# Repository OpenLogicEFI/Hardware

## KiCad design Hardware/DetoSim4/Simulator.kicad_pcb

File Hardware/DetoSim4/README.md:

# DetonStim

www.detonationems.com

Engine Simulator for Speeduino fork or Ardustim - https://github.com/speeduino/Ardu-Stim

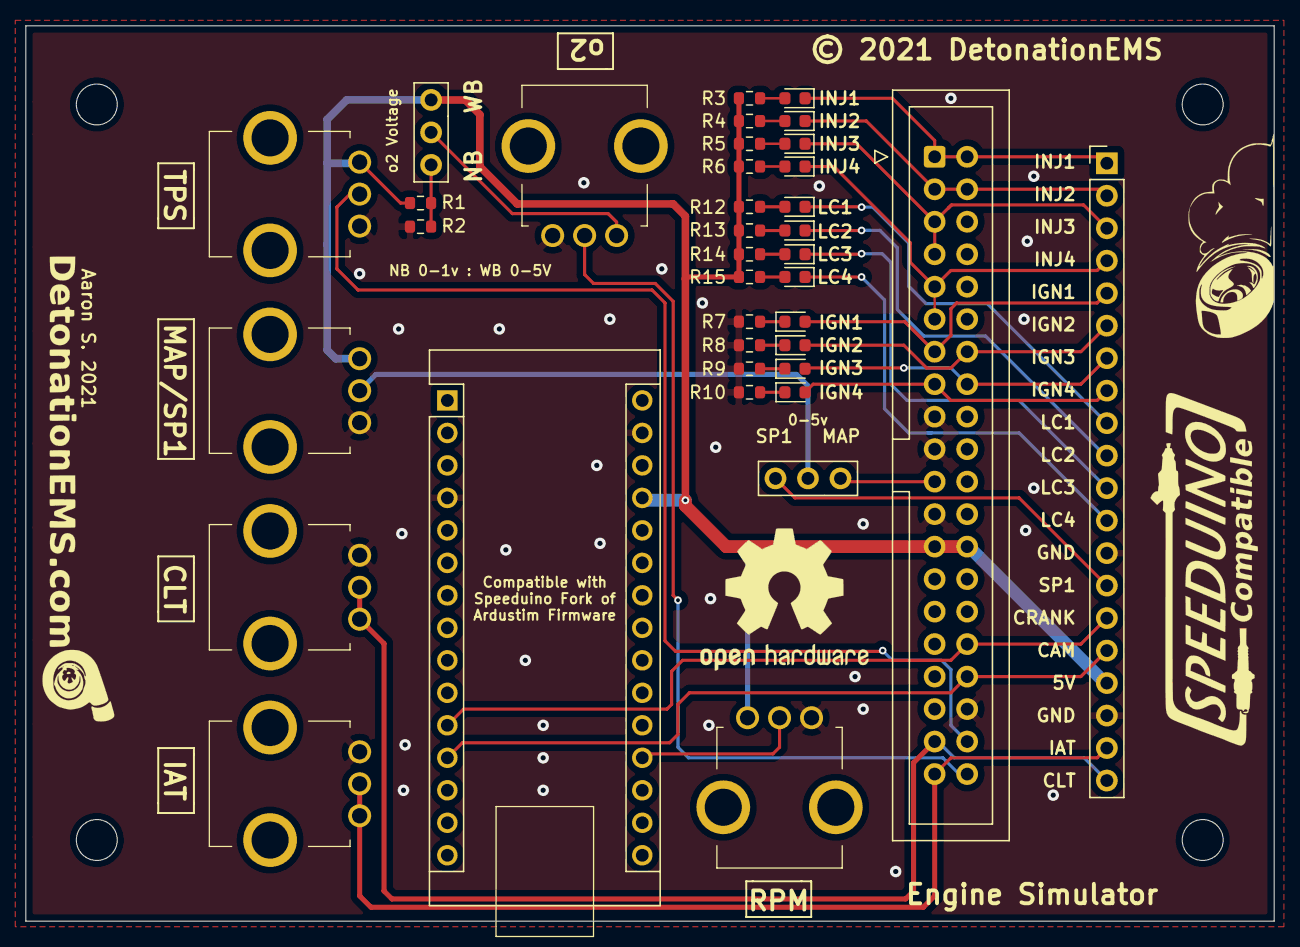
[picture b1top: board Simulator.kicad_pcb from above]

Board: 2 copper layers, 97.6 x 70.0 mm, 45 parts (0 on the bottom side), 38 nets.

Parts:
A1: Arduino_Nano_v3.x; Arduino_Nano
G1: Logo_Open_Hardware_Small; TireSmoke-22mm
G2: Logo_Open_Hardware_Small; DetonationEMS
G3: Logo_Open_Hardware_Small; SpeeduinoCompatible-30mm
G4: Logo_Open_Hardware_Small; OSHW-Logo2_14.6x12mm_SilkScreen
H1, H2, H3, H4: MountingHole; MountingHole_3.2mm_M3
J1, J8: Conn_01x03; 3-PinSwitch
J2: Conn_02x20_Counter_Clockwise; IDC-Header_2x20_P2.54mm_Vertical_Speeduino
J6: Header; PinHeader_1x20_P2.54mm_Vertical
LED1: INJ1; LED_0603_1608Metric
LED2: INJ2; LED_0603_1608Metric
LED3: INJ3; LED_0603_1608Metric
LED4: INJ4; LED_0603_1608Metric
LED5: IGN1; LED_0603_1608Metric
LED6: IGN2; LED_0603_1608Metric
LED7: IGN3; LED_0603_1608Metric
LED8: IGN4; LED_0603_1608Metric
LED10: IDLE; LED_0603_1608Metric
LED11: IDLE2; LED_0603_1608Metric
LED12: VVT; LED_0603_1608Metric
LED13: BOOST; LED_0603_1608Metric
POT1: IAT; RV09AF4020KB10K
POT2: CLT; RV09AF4020KB10K
POT3: TPS; RV09AF4020KB10K
POT4: MAP/SP1; RV09AF4020KB10K
POT5: o2; RV09AF4020KB10K
POT6: RPM; RV09AF4020KB10K
R1: 470; R_0603_1608Metric
R2: 100; R_0603_1608Metric
R3, R4, R5, R6, R7, R8, R9, R10, R12, R13, R14, R15: 330; R_0603_1608Metric

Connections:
+5V: A1.27, J1.1, J2.13, J2.28, J6.17, POT3.3, POT4.3, POT6.3, R1.1, R3.1, R4.1, R5.1, R6.1, R12.1, R13.1, R14.1, R15.1
CAM: A1.12, J2.24, J6.16
CLT: J2.19, J6.20, POT2.1, POT2.2
CRANK: A1.11, J2.25, J6.15
GND: A1.4, A1.29, J2.9, J2.10, J2.12, J2.23, J6.13, J6.18, POT1.3, POT2.3, POT3.1, POT4.1, POT5.1, POT6.1, R2.2, R7.1, R8.1, R9.1, R10.1
IAT: J2.20, J6.19, POT1.1, POT1.2
IGN1: J2.7, J6.5, LED5.2
IGN2: J2.34, J6.6, LED6.2
IGN3: J2.33, J6.7, LED7.2
IGN4: J2.8, J6.8, LED8.2
INJ1: J2.1, J2.40, J6.1, LED1.1
INJ2: J2.2, J2.39, J6.2, LED2.1
INJ3: J2.3, J2.4, J6.3, LED3.1
INJ4: J2.5, J2.6, J6.4, LED4.1
LC1: J6.9, LED10.1
LC2: J6.10, LED11.1
LC3: J6.11, LED12.1
LC4: J6.12, LED13.1
MAP: J2.11, J8.1
MC-A0: A1.19, POT6.2
unnamed: J1.3, R1.2, R2.1
unnamed: LED1.2, R3.2
unnamed: LED2.2, R4.2
unnamed: LED3.2, R5.2
unnamed: LED4.2, R6.2
unnamed: LED5.1, R7.2
unnamed: LED6.1, R8.2
unnamed: LED7.1, R9.2
unnamed: LED8.1, R10.2
unnamed: LED10.2, R12.2
unnamed: LED11.2, R13.2
unnamed: LED12.2, R14.2
unnamed: LED13.2, R15.2
RV4: J8.2, POT4.2
SP1: J6.14, J8.3
TPS: J2.22, POT3.2
o2: J2.21, POT5.2
o2-Voltage: J1.2, POT5.3

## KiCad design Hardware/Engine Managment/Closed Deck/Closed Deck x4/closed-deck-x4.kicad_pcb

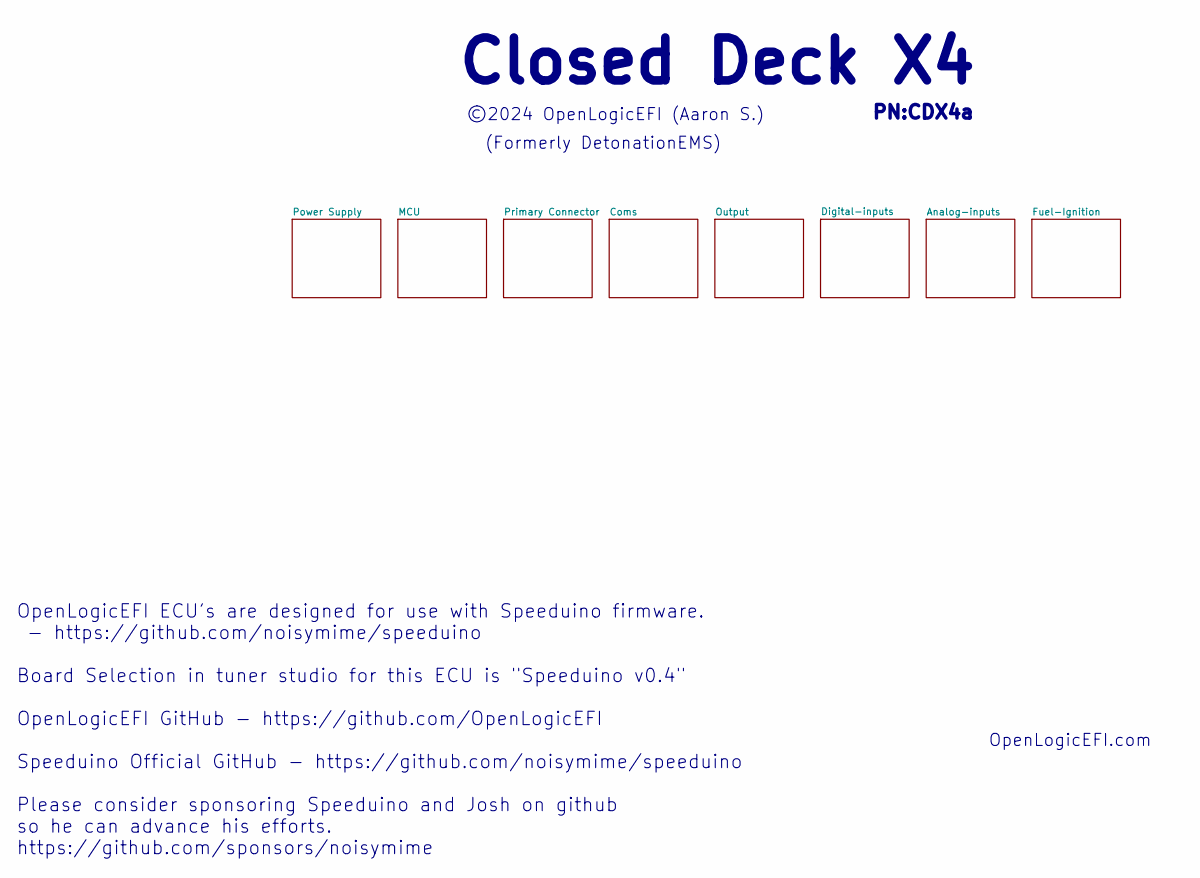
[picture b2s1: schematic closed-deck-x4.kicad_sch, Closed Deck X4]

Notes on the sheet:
©2024 OpenLogicEFI (Aaron S.)
(Formerly DetonationEMS)
OpenLogicEFI ECU's are designed for use with Speeduino firmware. - https://github.com/noisymime/speeduino Board Selection in tuner studio for this ECU is "Speeduino v0.4" OpenLogicEFI GitHub - https://github.com/OpenLogicEFI Speeduino Official GitHub - https://github.com/noisymime/speeduino Please 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
Closed Deck X4
PN:CDX4a
OpenLogicEFI.com

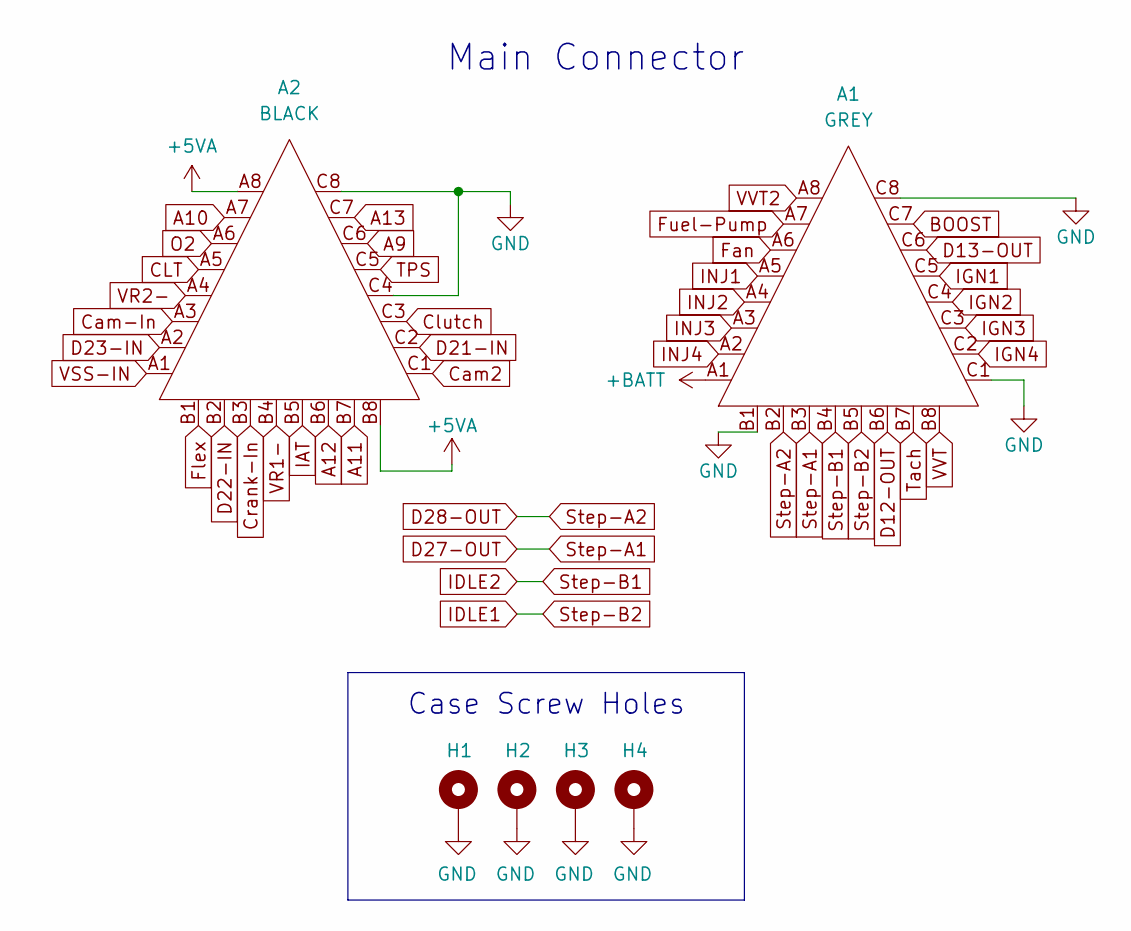
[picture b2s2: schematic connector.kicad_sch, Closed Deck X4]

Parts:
A1: GREY; Delphi_Sicma_24_Grey
A2: BLACK; Delphi_Sicma_24_Black
H1, H2, H3, H4: MountingHole_Pad; MountingHole_3.5mm_Pad

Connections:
+5V: A2.A8, A2.B8; also elsewhere on the board
+BATT: A1.A1; also elsewhere on the board
A9: A2.C6; also elsewhere on the board
A10: A2.A7; also elsewhere on the board
A11: A2.B7; also elsewhere on the board
A12: A2.B6; also elsewhere on the board
A13: A2.C7; also elsewhere on the board
BOOST: A1.C7; also elsewhere on the board
CLT: A2.A5; also elsewhere on the board
Cam2: A2.C1; also elsewhere on the board
Cam-In: A2.A3; also elsewhere on the board
Clutch: A2.C3; also elsewhere on the board
Crank-In: A2.B3; also elsewhere on the board
D12-OUT: A1.B6; also elsewhere on the board
D13-OUT: A1.C6; also elsewhere on the board
D21-IN: A2.C2; also elsewhere on the board
D22-IN: A2.B2; also elsewhere on the board
D23-IN: A2.A2; also elsewhere on the board
D27-OUT: A1.B3; also elsewhere on the board
D28-OUT: A1.B2; also elsewhere on the board
Fan: A1.A6; also elsewhere on the board
Flex: A2.B1; also elsewhere on the board
Fuel-Pump: A1.A7; also elsewhere on the board
GND: A1.B1, A1.C1, A1.C8, A2.C4, A2.C8, H1.1, H2.1, H3.1, H4.1; also elsewhere on the board
IAT: A2.B5; also elsewhere on the board
IDLE1: A1.B5; also elsewhere on the board
IDLE2: A1.B4; also elsewhere on the board
IGN1: A1.C5; also elsewhere on the board
IGN2: A1.C4; also elsewhere on the board
IGN3: A1.C3; also elsewhere on the board
IGN4: A1.C2; also elsewhere on the board
INJ1: A1.A5; also elsewhere on the board
INJ2: A1.A4; also elsewhere on the board
INJ3: A1.A3; also elsewhere on the board
INJ4: A1.A2; also elsewhere on the board
O2: A2.A6; also elsewhere on the board
TPS: A2.C5; also elsewhere on the board
Tach: A1.B7; also elsewhere on the board
VR1-: A2.B4; also elsewhere on the board
VR2-: A2.A4; also elsewhere on the board
VSS-IN: A2.A1; also elsewhere on the board
VVT: A1.B8; also elsewhere on the board
VVT2: A1.A8; also elsewhere on the board

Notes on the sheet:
Case Screw Holes
Main Connector

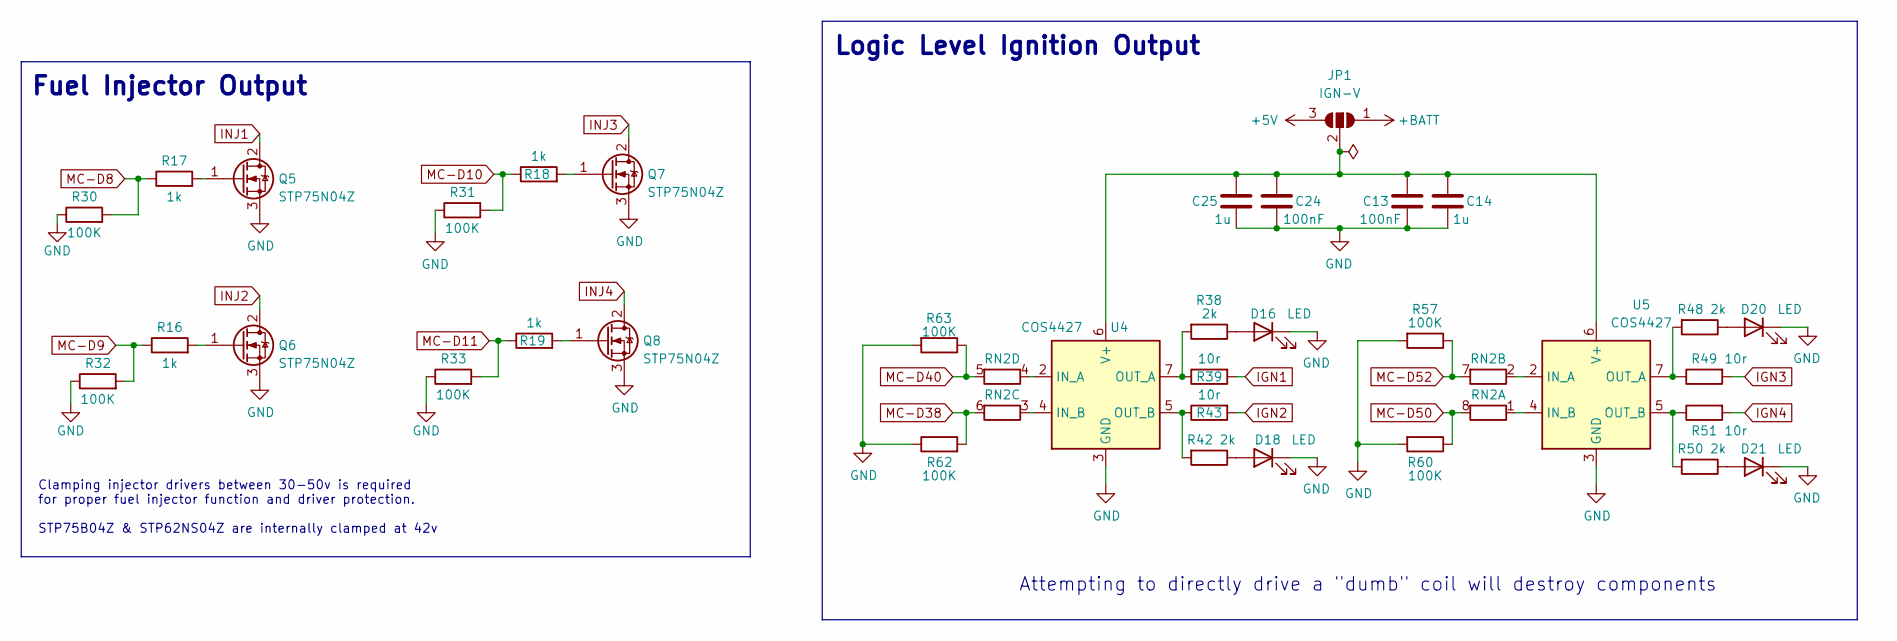
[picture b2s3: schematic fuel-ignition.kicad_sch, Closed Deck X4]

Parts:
C13, C24: 100nF; C_0402_1005Metric; LCSC C307331
C14, C25: 1u; C_0402_1005Metric; LCSC C52923
D16, D18, D20, D21: LED; LED_0603_1608Metric; Manufacture Part Number KT-0603R; LCSC C2286
JP1: IGN-V; 1x03-Proto
Q5, Q6, Q7, Q8: STP75N04Z; TO-220-3_Vertical
R16, R17, R18, R19: 1k; R_0402_1005Metric; Manufacture Part Number 0402WGF1001TCE; LCSC C11702
R30, R31, R32, R33, R57, R60, R62, R63: 100K; R_0402_1005Metric; Manufacture Part Number 0402WGF1003TCE; LCSC C25741
R38, R42, R48, R50: 2k; R_0402_1005Metric; Manufacture Part Number 0402WGF2001TCE; LCSC C4109
R39, R43, R49, R51: 10r; R_0805_2012Metric; Manufacture Part Number 0805W8F100JT5E; LCSC C17415
RN2: 1k; R_Array_Concave_4x0603; Manufacture Part Number 4D03WGJ0102T5E; LCSC C20197
U4, U5: COS4427; SOIC-8_3.9x4.9mm_P1.27mm; LCSC C2685358

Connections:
+5V: JP1.3 (B); also elsewhere on the board
+BATT: JP1.1 (A); also elsewhere on the board
GND: C13.2, C14.2, C24.2, C25.2, D16.1 (K), D18.1 (K), D20.1 (K), D21.1 (K), Q5.3 (S), Q6.3 (S), Q7.3 (S), Q8.3 (S), R30.1, R31.1, R32.1, R33.1, R57.2, R60.2, R62.1, R63.2, U4.3 (GND), U5.3 (GND); also elsewhere on the board
IGN1: R39.2; also elsewhere on the board
IGN2: R43.2; also elsewhere on the board
IGN3: R49.2; also elsewhere on the board
IGN4: R51.2; also elsewhere on the board
INJ1: Q5.2 (D); also elsewhere on the board
INJ2: Q6.2 (D); also elsewhere on the board
INJ3: Q7.2 (D); also elsewhere on the board
INJ4: Q8.2 (D); also elsewhere on the board
MC-D8: R17.1, R30.2; also elsewhere on the board
MC-D9: R16.1, R32.2; also elsewhere on the board
MC-D10: R18.1, R31.2; also elsewhere on the board
MC-D11: R19.1, R33.2; also elsewhere on the board
MC-D38: R62.2, RN2.6 (R3.2); also elsewhere on the board
MC-D40: R63.1, RN2.5 (R4.2); also elsewhere on the board
MC-D50: R60.1, RN2.8 (R1.2); also elsewhere on the board
MC-D52: R57.1, RN2.7 (R2.2); also elsewhere on the board
unnamed: D16.2 (A), R38.1
unnamed: D18.2 (A), R42.1
unnamed: D20.2 (A), R48.1
unnamed: D21.2 (A), R50.1
unnamed: C13.1, C14.1, C24.1, C25.1, JP1.2 (C), U4.6 (V+), U5.6 (V+)
unnamed: Q5.1 (G), R17.2
unnamed: Q6.1 (G), R16.2
unnamed: Q7.1 (G), R18.2
unnamed: Q8.1 (G), R19.2
unnamed: RN2.1 (R1.1), U5.4 (IN_B)
unnamed: RN2.2 (R2.1), U5.2 (IN_A)
unnamed: RN2.3 (R3.1), U4.4 (IN_B)
unnamed: RN2.4 (R4.1), U4.2 (IN_A)
unnamed: R38.2, R39.1, U4.7 (OUT_A)
unnamed: R42.2, R43.1, U4.5 (OUT_B)
unnamed: R48.2, R49.1, U5.7 (OUT_A)
unnamed: R50.2, R51.1, U5.5 (OUT_B)

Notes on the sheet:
Clamping injector drivers between 30-50v is required for proper fuel injector function and driver protection. STP75B04Z & STP62NS04Z are internally clamped at 42v
Fuel Injector Output
Logic Level Ignition Output
Attempting to directly drive a "dumb" coil will destroy components

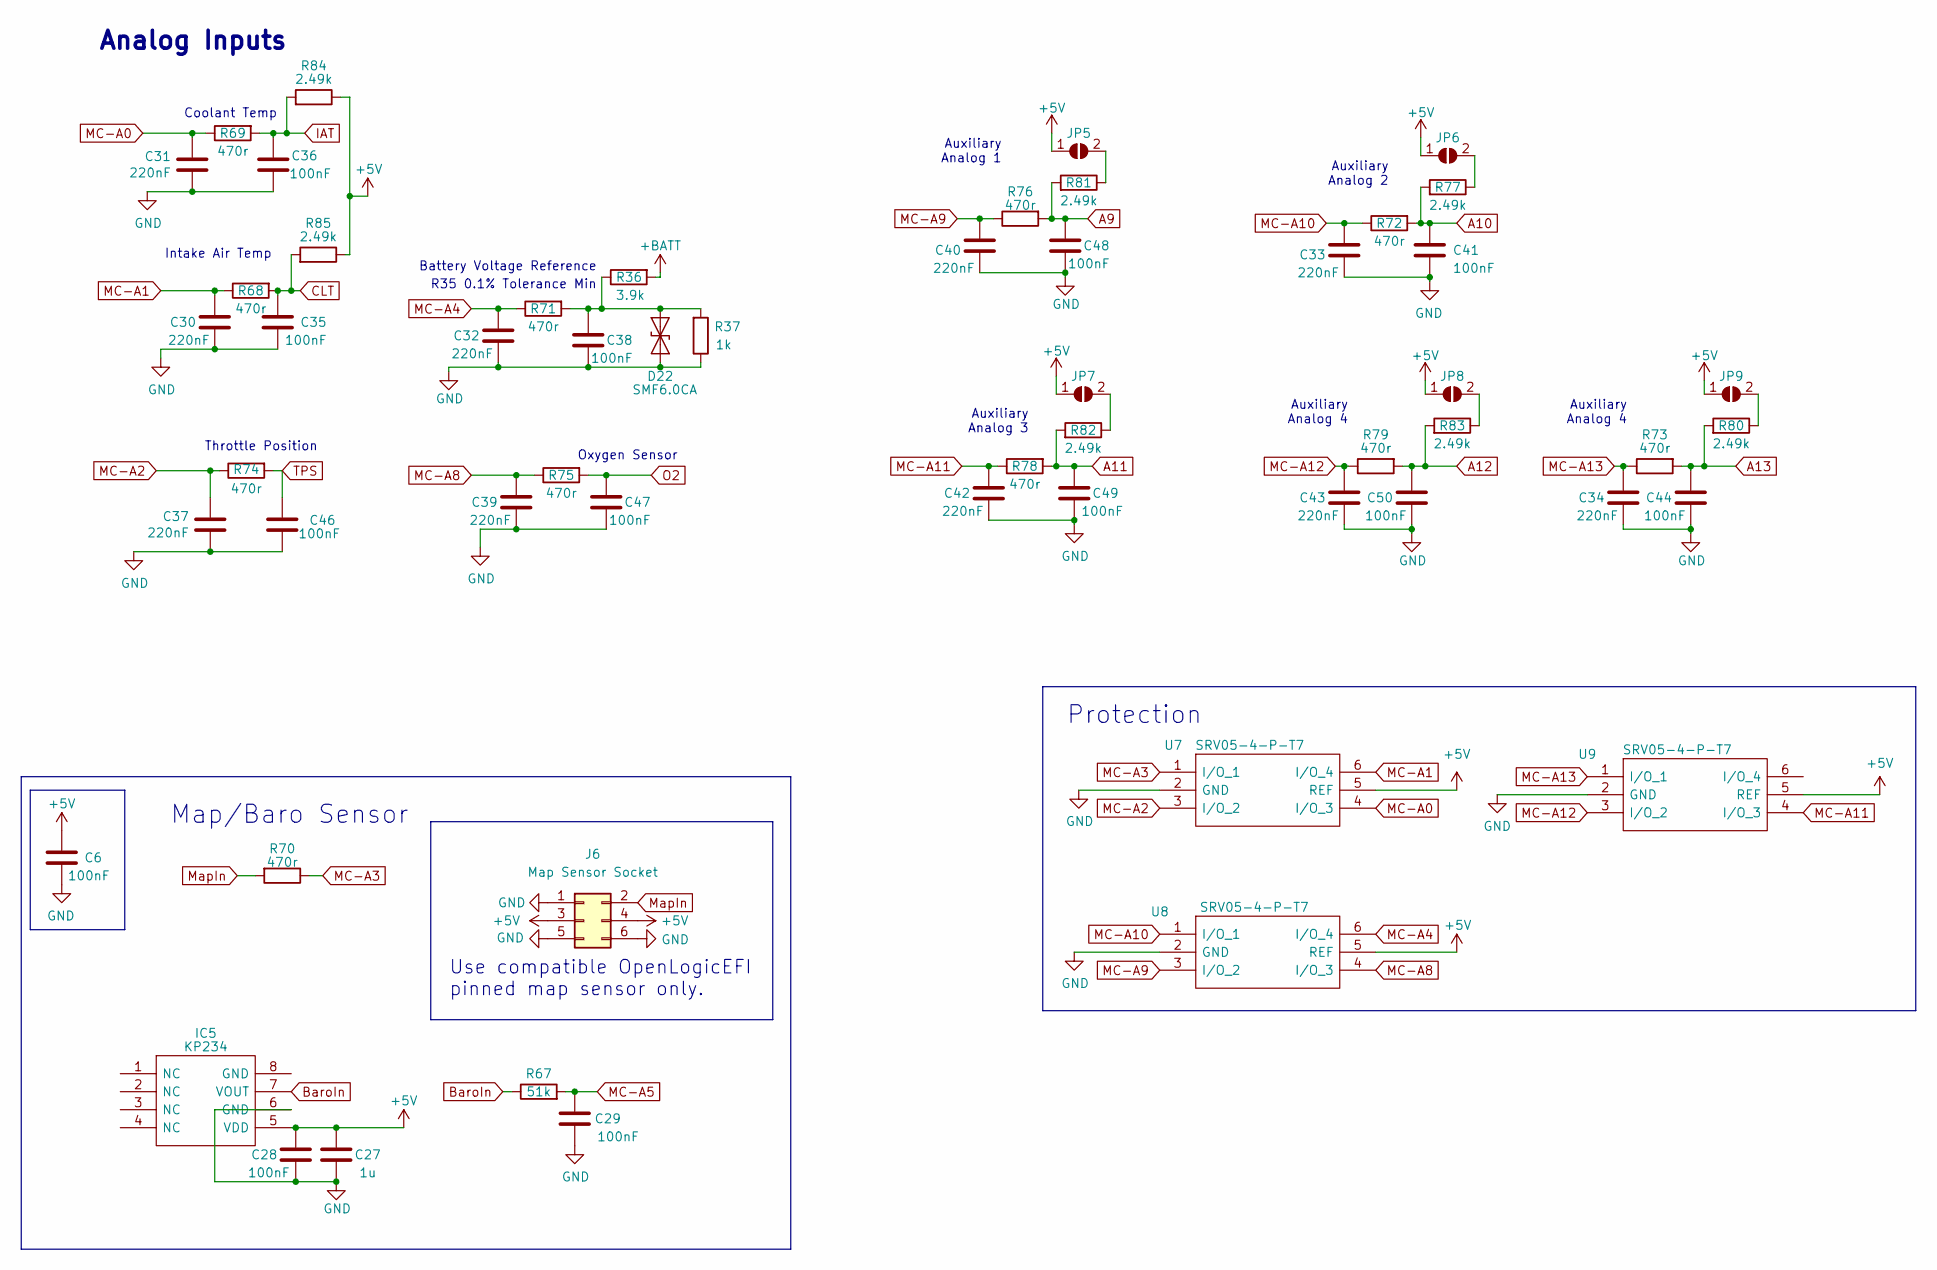
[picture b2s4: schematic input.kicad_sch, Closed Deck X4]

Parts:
C6, C28, C35, C36, C38, C41, C44, C46, C47, C48, C49, C50: 100nF; C_0402_1005Metric; LCSC C307331
C27: 1u; C_0402_1005Metric; LCSC C52923
C29: 100nF; C_0402_1005Metric; Manufacture Part Number CL05B104KB54PNC; LCSC C307331
C30, C31, C32, C33, C34, C37, C39, C40, C42, C43: 220nF; C_0402_1005Metric; LCSC C16772
D22: SMF6.0CA; D_SOD-123F; LCSC C2990473
IC5: KP234; KP234-Handsoldering; Mouser Part Number 726-KP234XTMA1
J6: Map Sensor Socket; PinSocket 2x03
JP5, JP6, JP7, JP8, JP9: SolderJumper_2_Open; SolderJumper-2_P1.3mm_Open_RoundedPad1.0x1.5mm
R36: 3.9k; R_0603_1608Metric; Manufacture Part Number 0603WAF3901T5E; LCSC C23018
R37: 1k; R_0402_1005Metric; Manufacture Part Number 0402WGF1001TCE; LCSC C11702
R67: 51k; R_0402_1005Metric; Manufacture Part Number 0402WGF5102TCE; LCSC C25794
R68, R69, R70, R71, R72, R73, R74, R75, R76, R78, R79: 470r; R_0402_1005Metric; Manufacture Part Number 0402WGF4700TCE; LCSC C25117
R77, R80, R81, R82, R83, R84, R85: 2.49k; R_0402_1005Metric; Manufacture Part Number RC0402FR-072K49L; LCSC C145071
U7, U8, U9: SRV05-4-P-T7; SOT-23-6; LCSC C85364

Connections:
+5V: C6.2, C27.1, C28.1, IC5.5 (VDD), J6.3, J6.4, JP5.1 (A), JP6.1 (A), JP7.1 (A), JP8.1 (A), JP9.1 (A), R84.1, R85.1, U7.5 (REF), U8.5 (REF), U9.5 (REF); also elsewhere on the board
+BATT: R36.2; also elsewhere on the board
A9: C48.1, R76.2, R81.2; also elsewhere on the board
A10: C41.1, R72.2, R77.2; also elsewhere on the board
A11: C49.1, R78.2, R82.2; also elsewhere on the board
A12: C50.1, R79.2, R83.2; also elsewhere on the board
A13: C44.1, R73.2, R80.2; also elsewhere on the board
BaroIn: IC5.7 (VOUT), R67.1
CLT: C35.1, R68.2, R85.2; also elsewhere on the board
GND: C6.1, C27.2, C28.2, C29.2, C30.2, C31.2, C32.2, C33.2, C34.2, C35.2, C36.2, C37.2, C38.2, C39.2, C40.2, C41.2, C42.2, C43.2, C44.2, C46.2, C47.2, C48.2, C49.2, C50.2, D22.2 (A2), IC5.6 (GND), J6.1, J6.5, J6.6, R37.1, U7.2 (GND), U8.2 (GND), U9.2 (GND); also elsewhere on the board
IAT: C36.1, R69.2, R84.2; also elsewhere on the board
MC-A0: C31.1, R69.1, U7.4 (I/O_3); also elsewhere on the board
MC-A1: C30.1, R68.1, U7.6 (I/O_4); also elsewhere on the board
MC-A2: C37.1, R74.1, U7.3 (I/O_2); also elsewhere on the board
MC-A3: R70.1, U7.1 (I/O_1); also elsewhere on the board
MC-A4: C32.1, R71.1, U8.6 (I/O_4); also elsewhere on the board
MC-A5: C29.1, R67.2; also elsewhere on the board
MC-A8: C39.1, R75.1, U8.4 (I/O_3); also elsewhere on the board
MC-A9: C40.1, R76.1, U8.3 (I/O_2); also elsewhere on the board
MC-A10: C33.1, R72.1, U8.1 (I/O_1); also elsewhere on the board
MC-A11: C42.1, R78.1, U9.4 (I/O_3); also elsewhere on the board
MC-A12: C43.1, R79.1, U9.3 (I/O_2); also elsewhere on the board
MC-A13: C34.1, R73.1, U9.1 (I/O_1); also elsewhere on the board
MapIn: J6.2, R70.2
unnamed: C38.1, D22.1 (A1), R36.1, R37.2, R71.2
unnamed: JP5.2 (B), R81.1
unnamed: JP6.2 (B), R77.1
unnamed: JP7.2 (B), R82.1
unnamed: JP8.2 (B), R83.1
unnamed: JP9.2 (B), R80.1
O2: C47.1, R75.2; also elsewhere on the board
TPS: C46.1, R74.2; also elsewhere on the board

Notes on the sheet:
Analog Inputs
Throttle Position
Auxiliary Analog 2
Auxiliary Analog 4
Auxiliary Analog 1
R35 0.1% Tolerance Min
Oxygen Sensor
Map/Baro Sensor
Use compatible OpenLogicEFI pinned map sensor only.
Coolant Temp
Intake Air Temp
Battery Voltage Reference
Protection
Auxiliary Analog 3

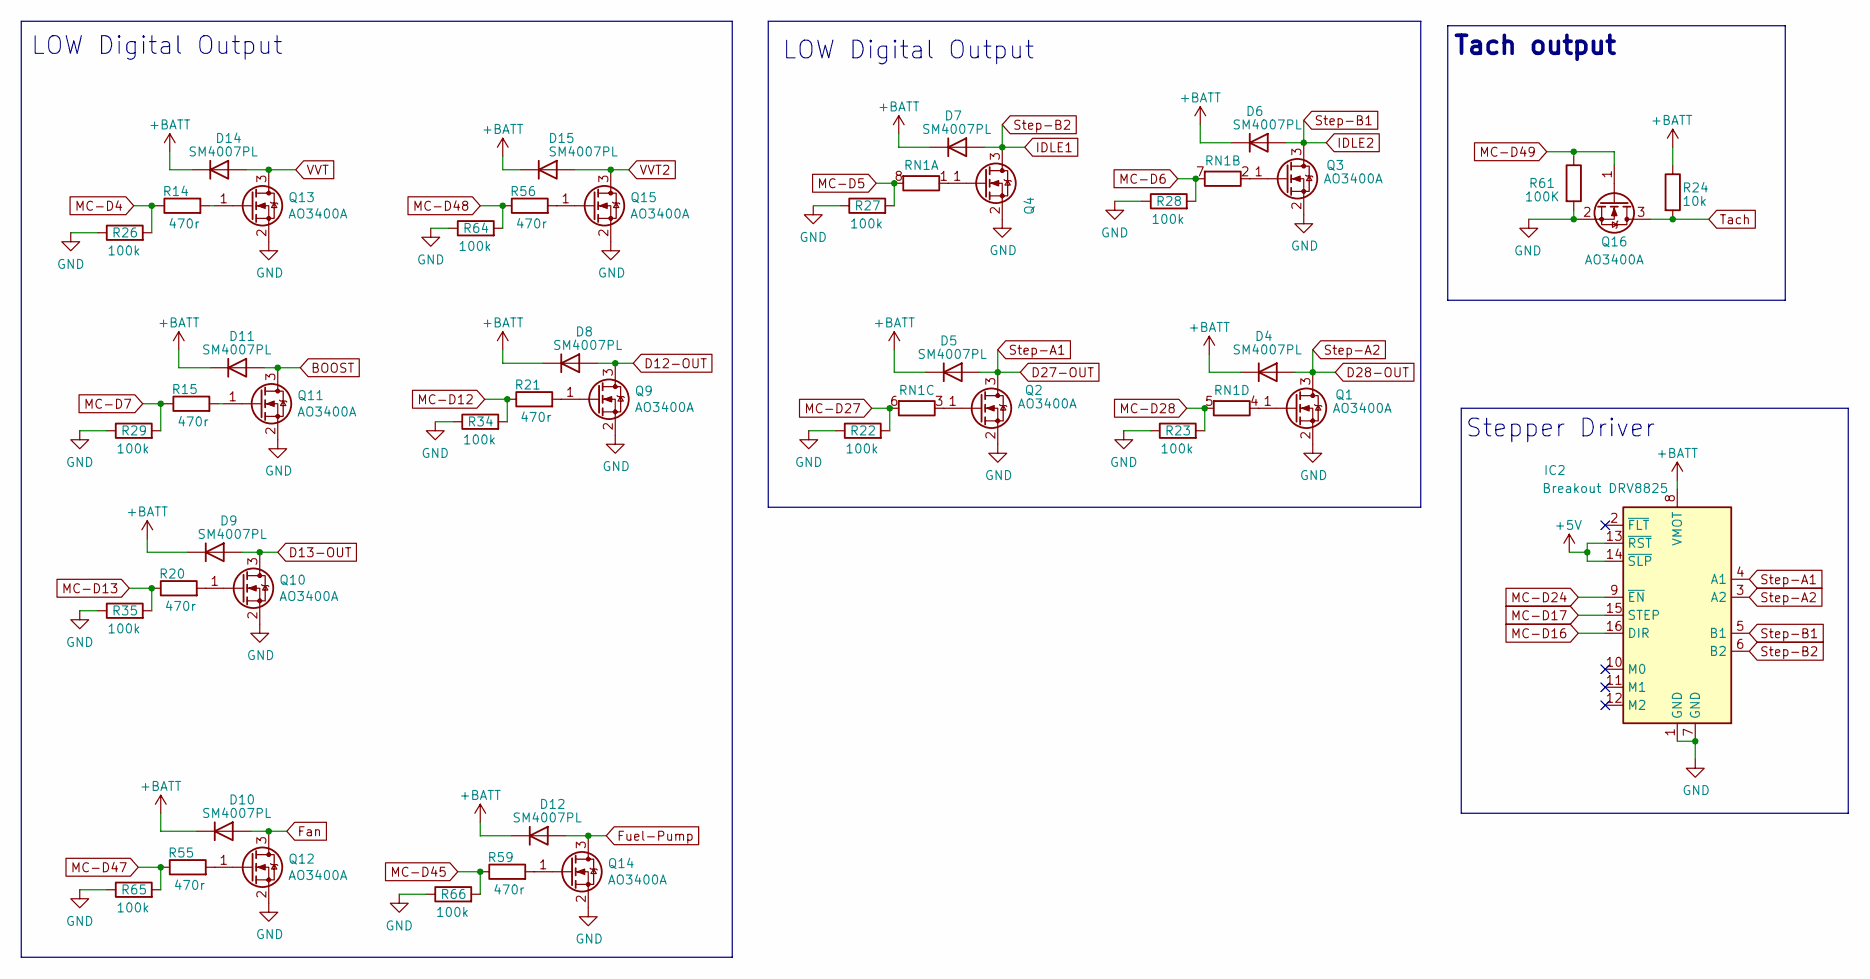
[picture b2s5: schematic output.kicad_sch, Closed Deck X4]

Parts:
D4, D5, D6, D7, D8, D9, D10, D11, D12, D14, D15: SM4007PL; D_SOD-123F; JLC C2128
IC2: Breakout DRV8825; DVR8825-Labeled-Front
Q1, Q2, Q3, Q4, Q9, Q10, Q16: AO3400A; SOT-23; LCSC C20917
Q11, Q12, Q13, Q14, Q15: AO3400A; SOT-23; JLC C20917
R14, R15, R20, R21, R55, R56, R59: 470r; R_0402_1005Metric; Manufacture Part Number 0402WGF4700TCE; LCSC C25117
R22, R23, R26, R27, R28, R29, R34, R35, R64, R65, R66: 100k; R_0402_1005Metric; Manufacture Part Number 0402WGF1003TCE; LCSC C25741
R24: 10k; R_0402_1005Metric; Manufacture Part Number 0402WGF1002TCE; LCSC C25744
R61: 100K; R_0402_1005Metric; Manufacture Part Number 0402WGF1003TCE; LCSC C25741
RN1: 1k; R_Array_Concave_4x0603; Manufacture Part Number 4D03WGJ0102T5E; LCSC C20197

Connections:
+5V: IC2.13 (~RST), IC2.14 (~SLP); also elsewhere on the board
+BATT: D4.1 (K), D5.1 (K), D6.1 (K), D7.1 (K), D8.1 (K), D9.1 (K), D10.1 (K), D11.1 (K), D12.1 (K), D14.1 (K), D15.1 (K), IC2.8 (VMOT), R24.1; also elsewhere on the board
BOOST: D11.2 (A), Q11.3 (D); also elsewhere on the board
D12-OUT: D8.2 (A), Q9.3 (D); also elsewhere on the board
D13-OUT: D9.2 (A), Q10.3 (D); also elsewhere on the board
D27-OUT: D5.2 (A), IC2.4 (A1), Q2.3 (D); also elsewhere on the board
D28-OUT: D4.2 (A), IC2.3 (A2), Q1.3 (D); also elsewhere on the board
Fan: D10.2 (A), Q12.3 (D); also elsewhere on the board
Fuel-Pump: D12.2 (A), Q14.3 (D); also elsewhere on the board
GND: IC2.1 (GND), IC2.7 (GND), Q1.2 (S), Q2.2 (S), Q3.2 (S), Q4.2 (S), Q9.2 (S), Q10.2 (S), Q11.2 (S), Q12.2 (S), Q13.2 (S), Q14.2 (S), Q15.2 (S), Q16.2 (S), R22.1, R23.1, R26.1, R27.1, R28.1, R29.1, R34.1, R35.1, R61.2, R64.1, R65.1, R66.1; also elsewhere on the board
IDLE1: D7.2 (A), IC2.6 (B2), Q4.3 (D); also elsewhere on the board
IDLE2: D6.2 (A), IC2.5 (B1), Q3.3 (D); also elsewhere on the board
MC-D4: R14.1, R26.2; also elsewhere on the board
MC-D5: R27.2, RN1.8 (R1.2); also elsewhere on the board
MC-D6: R28.2, RN1.7 (R2.2); also elsewhere on the board
MC-D7: R15.1, R29.2; also elsewhere on the board
MC-D12: R21.1, R34.2; also elsewhere on the board
MC-D13: R20.1, R35.2; also elsewhere on the board
MC-D16: IC2.16 (DIR); also elsewhere on the board
MC-D17: IC2.15 (STEP); also elsewhere on the board
MC-D24: IC2.9 (~EN); also elsewhere on the board
MC-D27: R22.2, RN1.6 (R3.2); also elsewhere on the board
MC-D28: R23.2, RN1.5 (R4.2); also elsewhere on the board
MC-D45: R59.1, R66.2; also elsewhere on the board
MC-D47: R55.1, R65.2; also elsewhere on the board
MC-D48: R56.1, R64.2; also elsewhere on the board
MC-D49: Q16.1 (G), R61.1; also elsewhere on the board
unnamed: Q1.1 (G), RN1.4 (R4.1)
unnamed: Q2.1 (G), RN1.3 (R3.1)
unnamed: Q3.1 (G), RN1.2 (R2.1)
unnamed: Q4.1 (G), RN1.1 (R1.1)
unnamed: Q9.1 (G), R21.2
unnamed: Q10.1 (G), R20.2
unnamed: Q11.1 (G), R15.2
unnamed: Q12.1 (G), R55.2
unnamed: Q13.1 (G), R14.2
unnamed: Q14.1 (G), R59.2
unnamed: Q15.1 (G), R56.2
Tach: Q16.3 (D), R24.2; also elsewhere on the board
VVT: D14.2 (A), Q13.3 (D); also elsewhere on the board
VVT2: D15.2 (A), Q15.3 (D); also elsewhere on the board

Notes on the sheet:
Tach output
LOW Digital Output
Stepper Driver

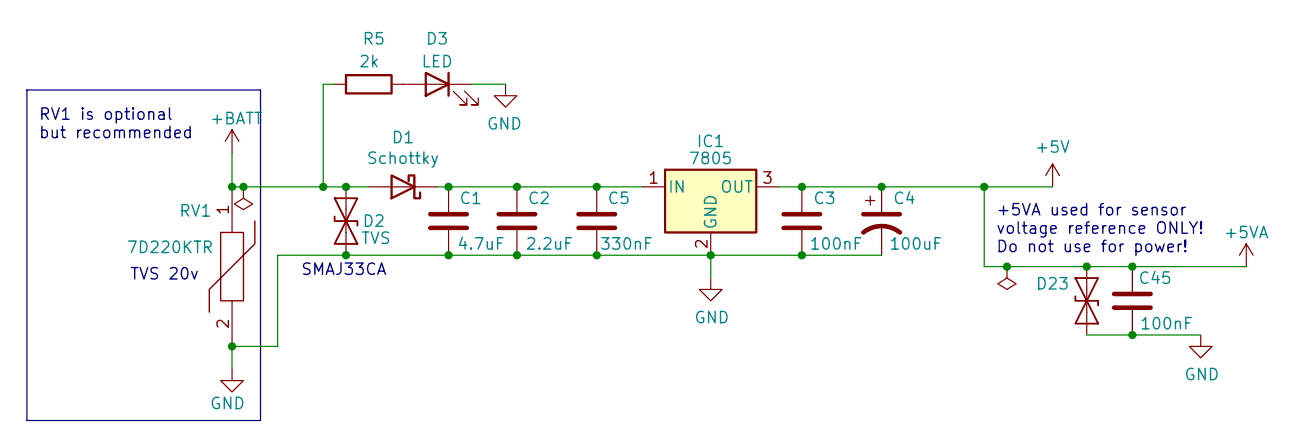
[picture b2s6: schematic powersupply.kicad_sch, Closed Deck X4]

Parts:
C1: 4.7uF; C_1206_3216Metric; Manufacture Part Number 1206B475K500NT; LCSC C29823
C2: 2.2uF; C_1206_3216Metric; Manufacture Part Number CL31B225KBHNNNE; LCSC C50254
C3, C45: 100nF; C_0805_2012Metric; Manufacture Part Number CC0805KRX7R9BB104; LCSC C49678
C4: 100uF; CP_EIA-3528-15_AVX-H; Manufacture Part Number TAJB107K006RNJ; LCSC C16133
C5: 330nF; C_0805_2012Metric; Manufacture Part Number 0805B334K500NT; LCSC C1740
D1: Schottky; D_SMA; Manufacture Part Number SS54; LCSC C22452
D2: TVS; D_SMA; Manufacture Part Number P6SMAJ33CA; LCSC C3019524
D3: LED; LED_0603_1608Metric; Manufacture Part Number KT-0603R; LCSC C2286
D23: SMF6.0CA; D_SOD-123F; LCSC C2990473
IC1: 7805; TO-252-2-Thermal-with-Silk; Manufacture Part Number L78M05ABDT-TR; LCSC C58069
R5: 2k; R_0402_1005Metric; Manufacture Part Number 0402WGF2001TCE; LCSC C4109
RV1: 7D220KTR; MOV07D220KTR

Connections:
+5V: C3.1, C4.1, C45.1, D23.2 (A2), IC1.3 (OUT); also elsewhere on the board
+BATT: D1.2 (A), D2.2 (A2), R5.2, RV1.1; also elsewhere on the board
GND: C1.2, C2.2, C3.2, C4.2, C5.2, C45.2, D2.1 (A1), D3.1 (K), D23.1 (A1), IC1.2 (GND), RV1.2; also elsewhere on the board
unnamed: C1.1, C2.1, C5.1, D1.1 (K), IC1.1 (IN)
unnamed: D3.2 (A), R5.1

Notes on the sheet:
TVS 20v
+5VA used for sensor voltage reference ONLY! Do not use for power!
SMAJ33CA
RV1 is optional but recommended

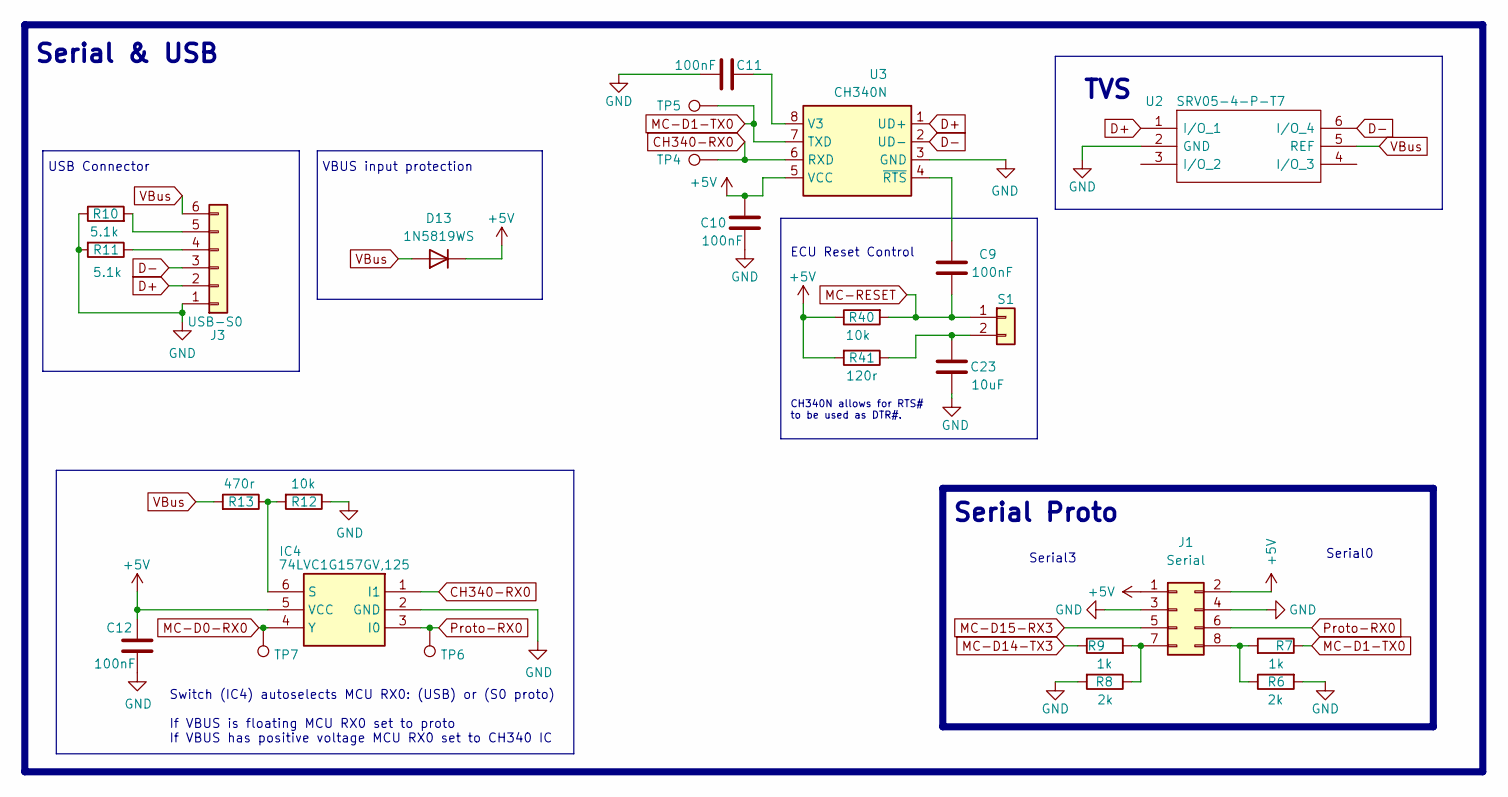
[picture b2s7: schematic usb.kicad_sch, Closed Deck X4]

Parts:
C9, C10, C11, C12: 100nF; C_0402_1005Metric; LCSC C307331
C23: 10uF; C_0603_1608Metric; Manufacture Part Number CL10A106KP8NNNC; LCSC C19702
D13: 1N5819WS; D_SOD-323; Manufacture Part Number 1N5819WS; LCSC C191023
IC4: 74LVC1G157GV,125; TSOT-23-6; Mouser Part Number 771-74LVC1G157GW-G
J1: Serial; 2x04-2.54mm-Proto-NoSilkscreen
J3: USB-S0; JST_PH_B6B-PH-K_1x06_P2.00mm_Vertical
R6, R8: 2k; R_0402_1005Metric; Manufacture Part Number 0402WGF2001TCE; LCSC C4109
R7, R9: 1k; R_0402_1005Metric; Manufacture Part Number 0402WGF1001TCE; LCSC C11702
R10, R11: 5.1k; R_0402_1005Metric; Manufacture Part Number 0402WGF5101TCE; LCSC C25905
R12, R40: 10k; R_0402_1005Metric; Manufacture Part Number 0402WGF1002TCE; LCSC C25744
R13: 470r; R_0402_1005Metric; Manufacture Part Number 0402WGF4700TCE; LCSC C25117
R41: 120r; R_0603_1608Metric; Manufacture Part Number 0402WGF4700TCE; LCSC C22787
S1: Reset Control; PinHeader_1x02_P2.54mm_Vertical
TP4, TP5, TP6, TP7: TestPoint; TestPoint_THT_D0.6mm_Drill0.3mm
U2: SRV05-4-P-T7; SOT-23-6; LCSC C85364
U3: CH340N; SOIC-8_3.9x4.9mm_P1.27mm

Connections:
+5V: C10.1, C12.2, D13.1 (K), IC4.5 (VCC), J1.1, J1.2, R40.1, R41.2, U3.5 (VCC); also elsewhere on the board
CH340-RX0: IC4.1 (I1), TP4.1, U3.6 (RXD)
D+: J3.2, U2.1 (I/O_1), U3.1 (UD+)
D-: J3.3, U2.6 (I/O_4), U3.2 (UD-)
GND: C10.2, C11.2, C12.1, C23.2, IC4.2 (GND), J1.3, J1.4, J3.1, R6.2, R8.2, R10.1, R11.2, R12.1, U2.2 (GND), U3.3 (GND); also elsewhere on the board
MC-D0-RX0: IC4.4 (Y), TP7.1; also elsewhere on the board
MC-D1-TX0: R7.1, TP5.1, U3.7 (TXD); also elsewhere on the board
MC-D14-TX3: R9.1; also elsewhere on the board
MC-D15-RX3: J1.5; also elsewhere on the board
MC-RESET: C9.2, R40.2, S1.1; also elsewhere on the board
unnamed: IC4.6 (S), R12.2, R13.1
unnamed: J1.7, R8.1, R9.2
unnamed: J1.8, R6.1, R7.2
unnamed: J3.4, R11.1
unnamed: J3.5, R10.2
unnamed: C23.1, R41.1, S1.2
unnamed: C11.1, U3.8 (V3)
unnamed: C9.1, U3.4 (~RTS)
Proto-RX0: IC4.3 (I0), J1.6, TP6.1
VBus: D13.2 (A), J3.6, R13.2, U2.5 (REF)

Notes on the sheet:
TVS
CH340N allows for RTS# to be used as DTR#.
VBUS input protection
Serial & USB
Serial Proto
Serial0
ECU Reset Control
Serial3
Switch (IC4) autoselects MCU RX0: (USB) or (S0 proto) If VBUS is floating MCU RX0 set to proto If VBUS has positive voltage MCU RX0 set to CH340 IC
USB Connector

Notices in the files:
Hardware/DetoSim4/Simulator.kicad_pcb:
© 2021 DetonationEMS
Hardware/Engine Managment/Pre-Ignition/Pre-Ignition x4/MX4B-2/Pre_Ignition.kicad_pcb:
© 2022 Aaron S.
Hardware/Engine Managment/Spark Gap/Spark Gap X4/RevC/Pre_Ignition.kicad_sch:
© 2025 OpenLogicEFI
